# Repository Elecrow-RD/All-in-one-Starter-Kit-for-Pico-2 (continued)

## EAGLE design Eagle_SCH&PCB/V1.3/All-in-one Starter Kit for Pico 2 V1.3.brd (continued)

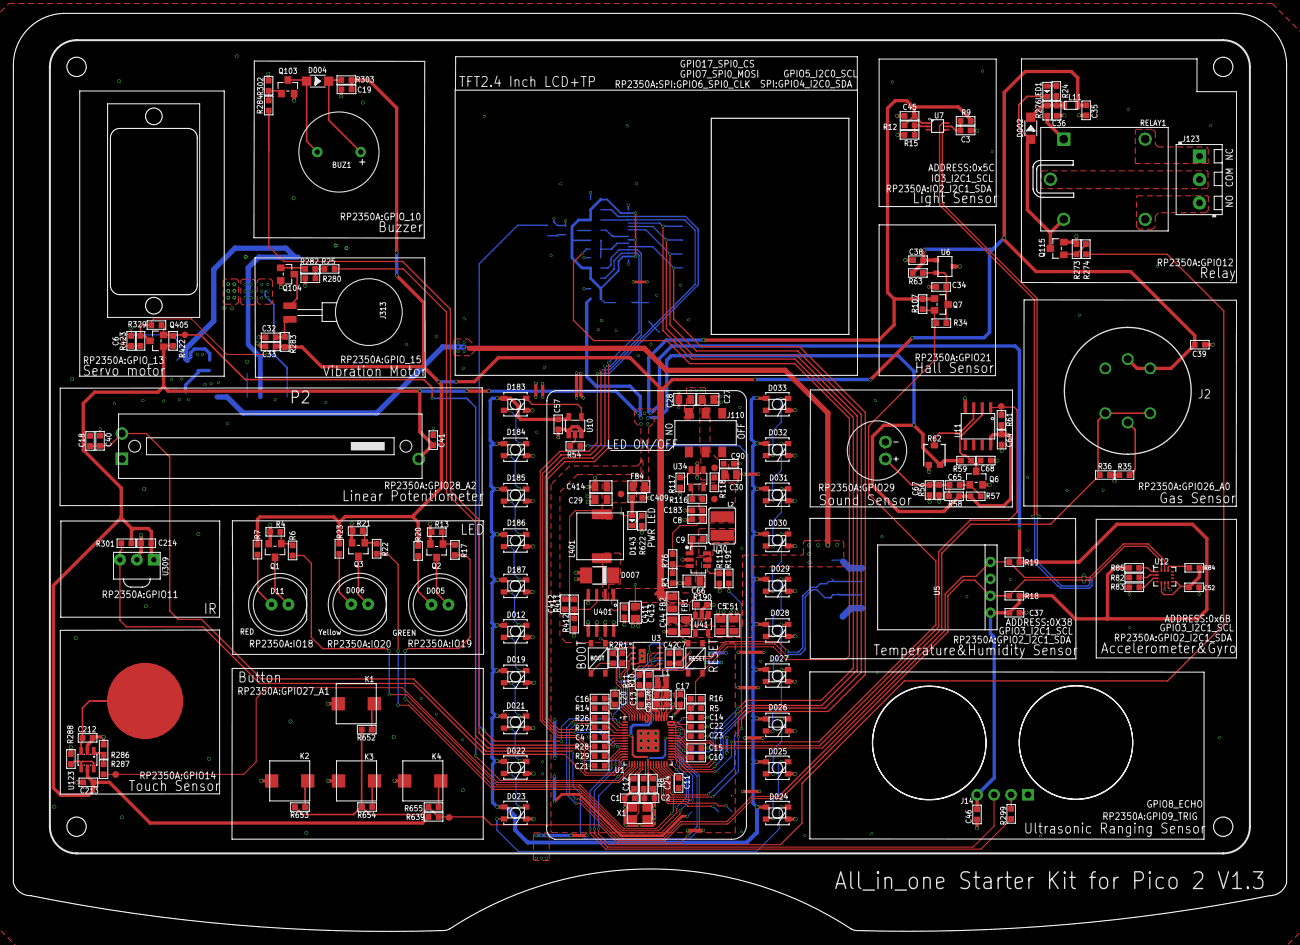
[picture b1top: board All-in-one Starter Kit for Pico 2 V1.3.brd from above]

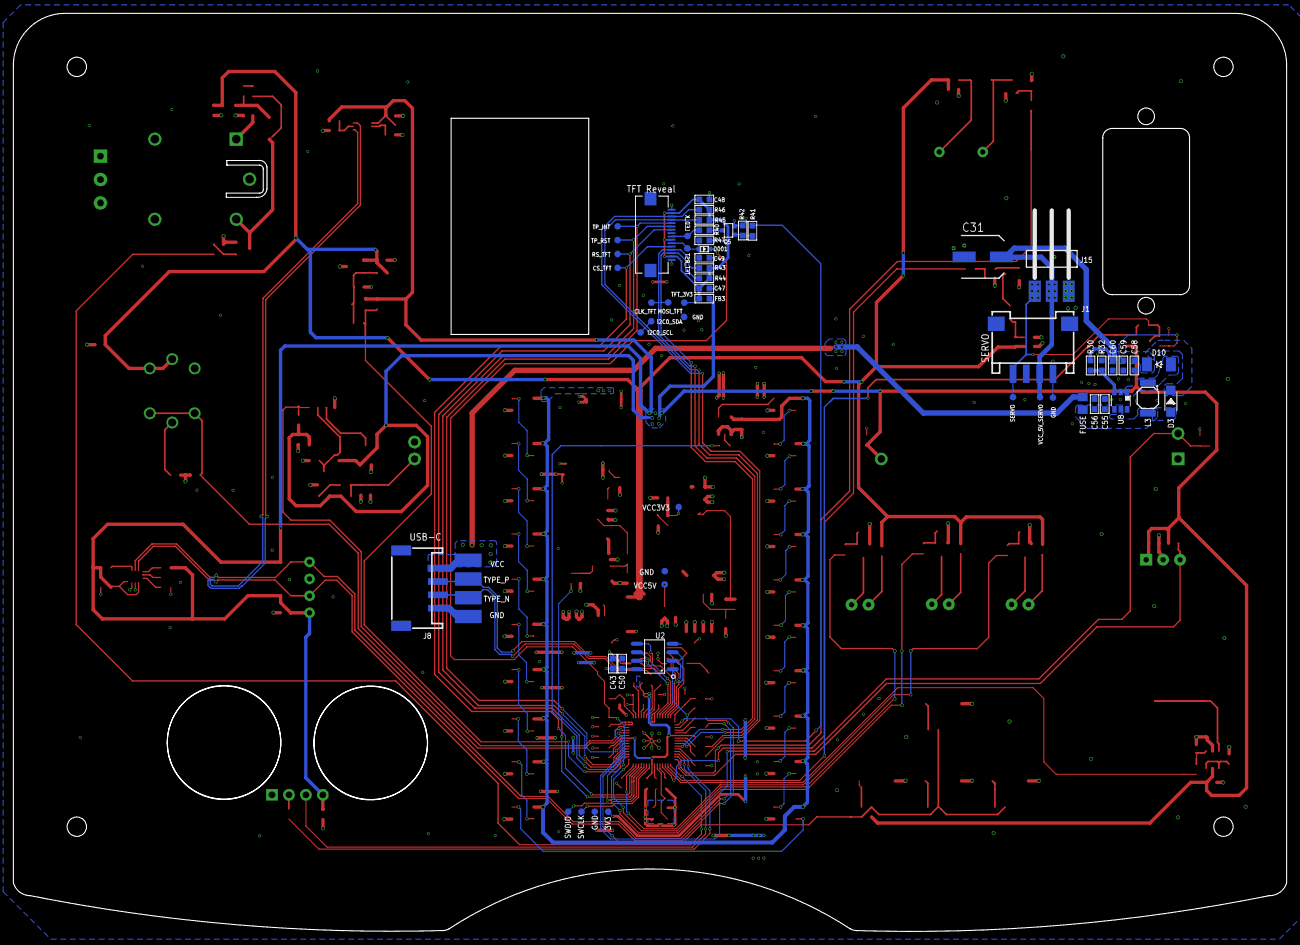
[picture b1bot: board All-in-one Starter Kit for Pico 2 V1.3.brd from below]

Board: 2 copper layers, 190.7 x 137.5 mm, 281 parts (60 on the bottom side), 148 nets.
